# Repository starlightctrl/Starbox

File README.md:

#### WIP Compact Integrated Rectangle Controller

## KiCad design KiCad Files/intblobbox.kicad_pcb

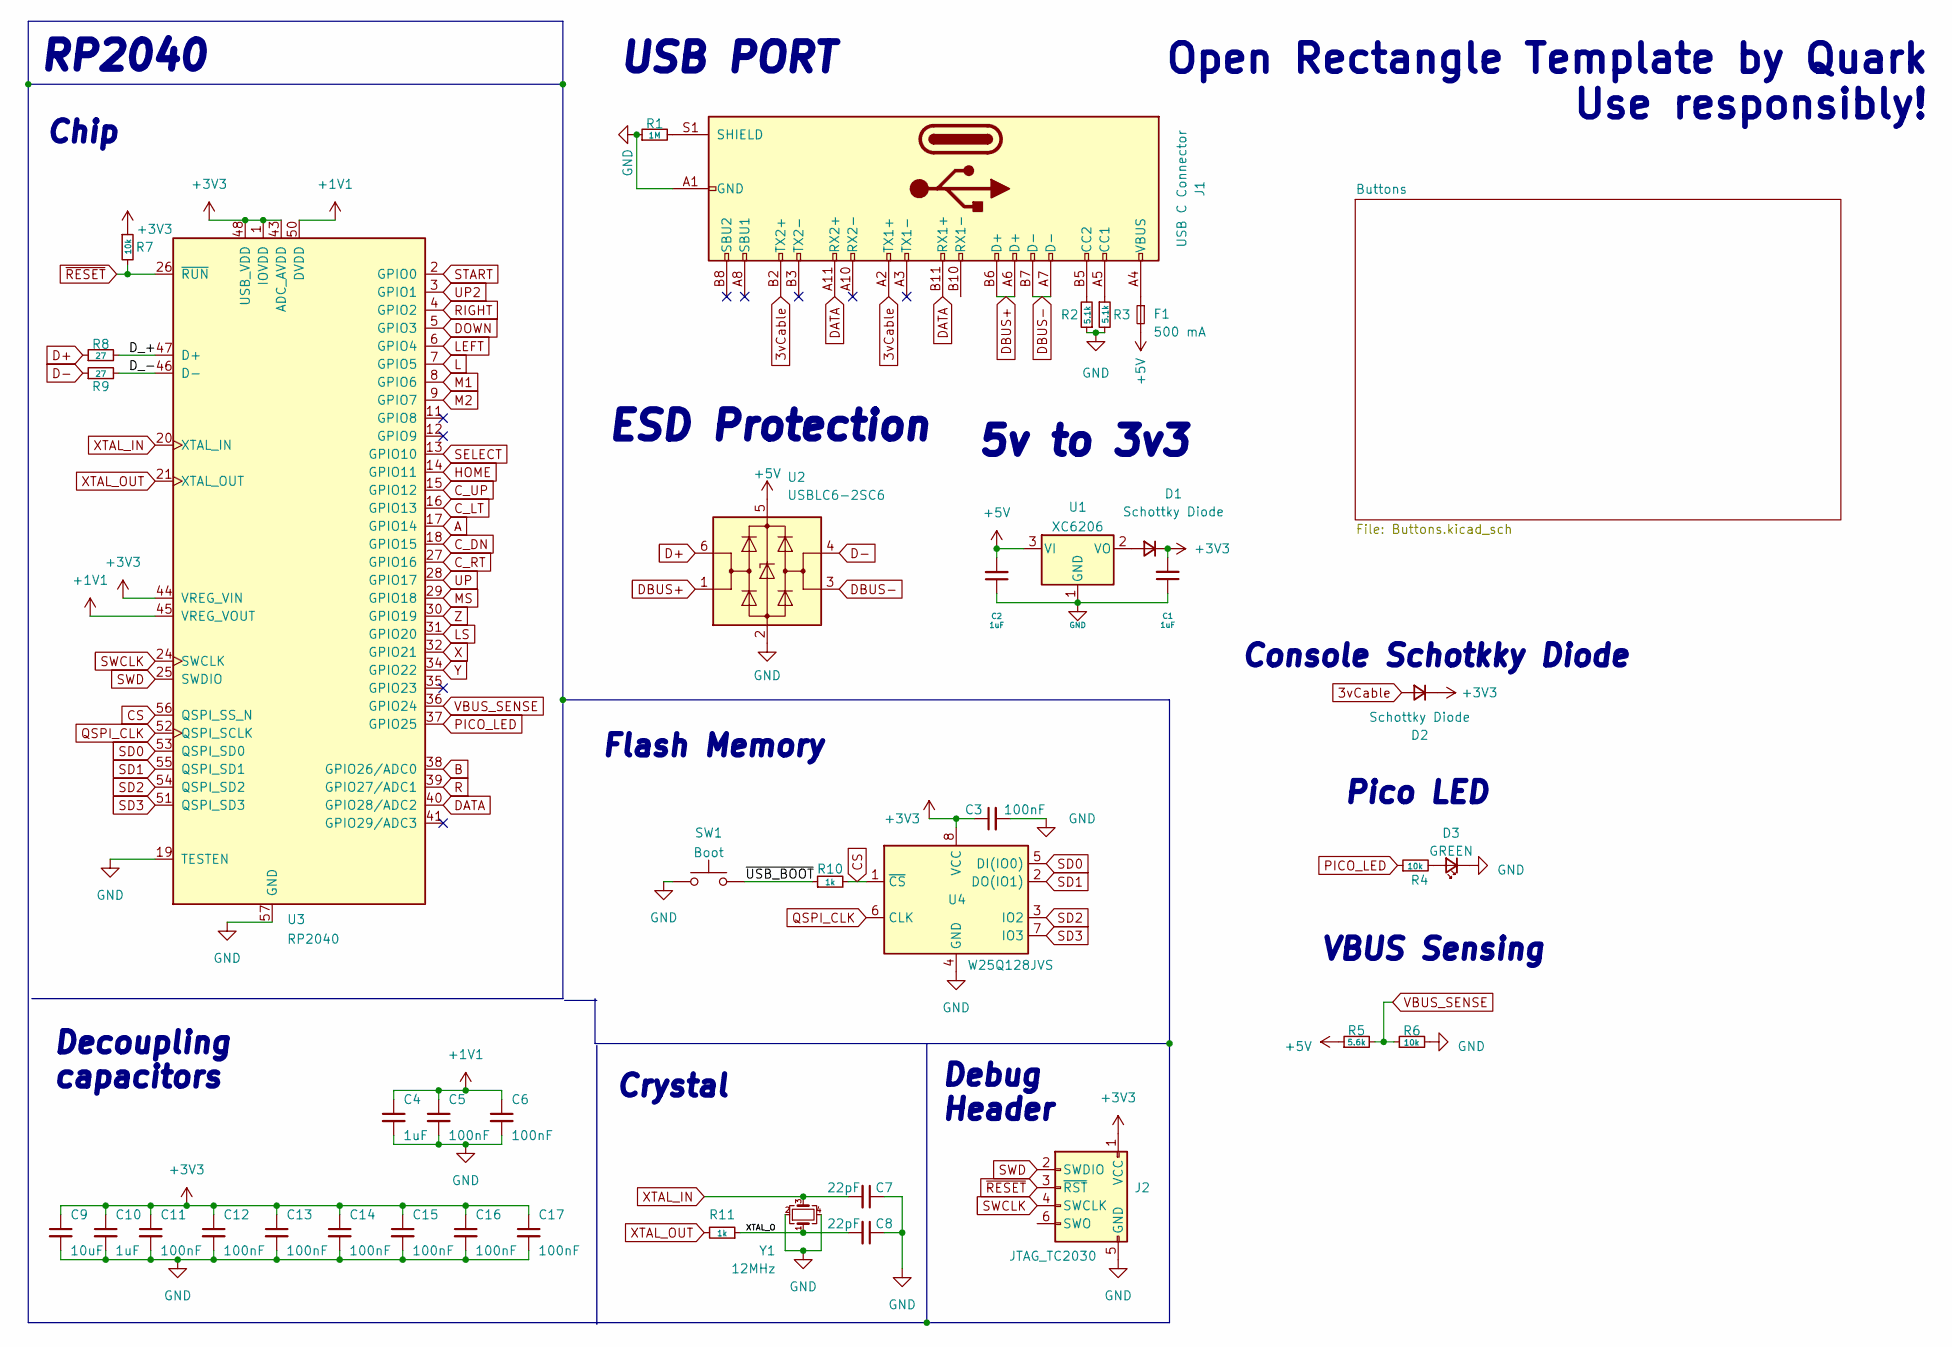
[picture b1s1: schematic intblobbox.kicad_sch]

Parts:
C1, C2, C4, C10: 1uF; C_0402_1005Metric; LCSC C52923
C3, C5, C6, C11, C12, C13, C14, C15, C16, C17: 100nF; C_0402_1005Metric; LCSC C1525
C7, C8: 22pF; C_0402_1005Metric; LCSC C1555
C9: 10uF; C_0402_1005Metric; LCSC C15525
D1, D2: Schottky Diode; D_SOD-123; LCSC C8598
D3: GREEN; LED_0805_2012Metric; LCSC C2297
F1: 500 mA; Fuse_1206_3216Metric; LCSC C70076
J1: USB C Connector; TYPE-C_24P_QCHT; LCSC C456013
J2: JTAG_TC2030; CON_TC2030_outlined
R1: 1M; R_0603_1608Metric; LCSC C22935
R2, R3: 5.1k; R_0402_1005Metric; LCSC C25905
R4, R7: 10k; R_0402_1005Metric; LCSC C25744
R5: 5.6k; R_0603_1608Metric; LCSC C23189
R6: 10k; R_0603_1608Metric; LCSC C25804
R8, R9: 27; R_0603_1608Metric; LCSC C25190
R10, R11: 1k; R_0402_1005Metric; LCSC C11702
SW1: Boot; SW_SPST_SKQG_WithStem; LCSC C318884
U1: XC6206; SOT-23; LCSC C5446
U2: USBLC6-2SC6; SOT-23-6; LCSC C7519
U3: RP2040; RP2040-QFN-56; LCSC C2040
U4: W25Q128JVS; SOIC-8_5.23x5.23mm_P1.27mm; LCSC C97521
Y1: 12MHz; Crystal_SMD_3225-4Pin_3.2x2.5mm; LCSC C9002

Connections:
3vCable: D2.2 (A), J1.A2 (TX1+), J1.B2 (TX2+)
+1V1: C4.1, C5.1, C6.1, U3.23 (DVDD), U3.45 (VREG_VOUT), U3.50 (DVDD)
+3V3: C1.2, C3.1, C9.1, C10.1, C11.1, C12.1, C13.1, C14.1, C15.1, C16.1, C17.1, D1.1 (K), D2.1 (K), J2.1 (VCC), R7.1, U3.1 (IOVDD), U3.10 (IOVDD), U3.22 (IOVDD), U3.33 (IOVDD), U3.42 (IOVDD), U3.43 (ADC_AVDD), U3.44 (VREG_VIN), U3.48 (USB_VDD), U3.49 (IOVDD), U4.8 (VCC)
+5V: C2.2, F1.2, R5.1, U1.3 (VI), U2.5 (VBUS)
/D_+: R8.2, U3.47 (D+)
/D_-: R9.2, U3.46 (D-)
/XTAL_O: C8.2, R11.1, Y1.1
/~USB_BOOT: R10.1, SW1.2
A: U3.17 (GPIO14); also elsewhere on the board
B: U3.38 (GPIO26/ADC0); also elsewhere on the board
CS: R10.2, U3.56 (QSPI_SS_N), U4.1 (~CS)
C_DN: U3.18 (GPIO15); also elsewhere on the board
C_LT: U3.16 (GPIO13); also elsewhere on the board
C_RT: U3.27 (GPIO16); also elsewhere on the board
C_UP: U3.15 (GPIO12); also elsewhere on the board
D+: R8.1, U2.6 (I/O1)
D-: R9.1, U2.4 (I/O2)
DATA: J1.A11 (RX2+), J1.B11 (RX1+), U3.40 (GPIO28/ADC2)
DBUS+: J1.A6 (D+), J1.B6 (D+), U2.1 (I/O1)
DBUS-: J1.A7 (D-), J1.B7 (D-), U2.3 (I/O2)
DOWN: U3.5 (GPIO3); also elsewhere on the board
GND: C1.1, C2.1, C3.2, C4.2, C5.2, C6.2, C7.1, C8.1, C9.2, C10.2, C11.2, C12.2, C13.2, C14.2, C15.2, C16.2, C17.2, D3.1 (K), J1.A1 (GND), J1.A12 (GND), J1.B1 (GND), J1.B12 (GND), J2.5 (GND), R1.1, R2.1, R3.2, R6.2, SW1.1, U1.1 (GND), U2.2 (GND), U3.19 (TESTEN), U3.57 (GND), U4.4 (GND), Y1.2, Y1.4; also elsewhere on the board
HOME: U3.14 (GPIO11); also elsewhere on the board
L: U3.7 (GPIO5); also elsewhere on the board
LEFT: U3.6 (GPIO4); also elsewhere on the board
LS: U3.31 (GPIO20); also elsewhere on the board
M1: U3.8 (GPIO6); also elsewhere on the board
M2: U3.9 (GPIO7); also elsewhere on the board
MS: U3.29 (GPIO18); also elsewhere on the board
unnamed: D1.2 (A), U1.2 (VO)
unnamed: D3.2 (A), R4.2
unnamed: F1.1, J1.A4 (VBUS), J1.A9 (VBUS), J1.B4 (VBUS), J1.B9 (VBUS)
unnamed: J1.A5 (CC1), R3.1
unnamed: J1.B5 (CC2), R2.2
unnamed: J1.S1 (SHIELD), R1.2
PICO_LED: R4.1, U3.37 (GPIO25)
QSPI_CLK: U3.52 (QSPI_SCLK), U4.6 (CLK)
R: U3.39 (GPIO27/ADC1); also elsewhere on the board
RIGHT: U3.4 (GPIO2); also elsewhere on the board
SD0: U3.53 (QSPI_SD0), U4.5 (DI(IO0))
SD1: U3.55 (QSPI_SD1), U4.2 (DO(IO1))
SD2: U3.54 (QSPI_SD2), U4.3 (IO2)
SD3: U3.51 (QSPI_SD3), U4.7 (IO3)
SELECT: U3.13 (GPIO10); also elsewhere on the board
START: U3.2 (GPIO0); also elsewhere on the board
SWCLK: J2.4 (SWCLK), U3.24 (SWCLK)
SWD: J2.2 (SWDIO), U3.25 (SWDIO)
UP: U3.28 (GPIO17); also elsewhere on the board
UP2: U3.3 (GPIO1); also elsewhere on the board
VBUS_SENSE: R5.2, R6.1, U3.36 (GPIO24)
X: U3.32 (GPIO21); also elsewhere on the board
XTAL_IN: C7.2, U3.20 (XTAL_IN), Y1.3
XTAL_OUT: R11.2, U3.21 (XTAL_OUT)
Y: U3.34 (GPIO22); also elsewhere on the board
Z: U3.30 (GPIO19); also elsewhere on the board
~RESET: J2.3 (~RST), R7.2, U3.26 (~RUN)

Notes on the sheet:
Console Schotkky Diode
Crystal
USB PORT
Flash Memory
Pico LED
Open Rectangle Template by Quark Use responsibly!
RP2040
Debug Header
VBUS Sensing
Chip
5v to 3v3
ESD Protection
Decoupling capacitors

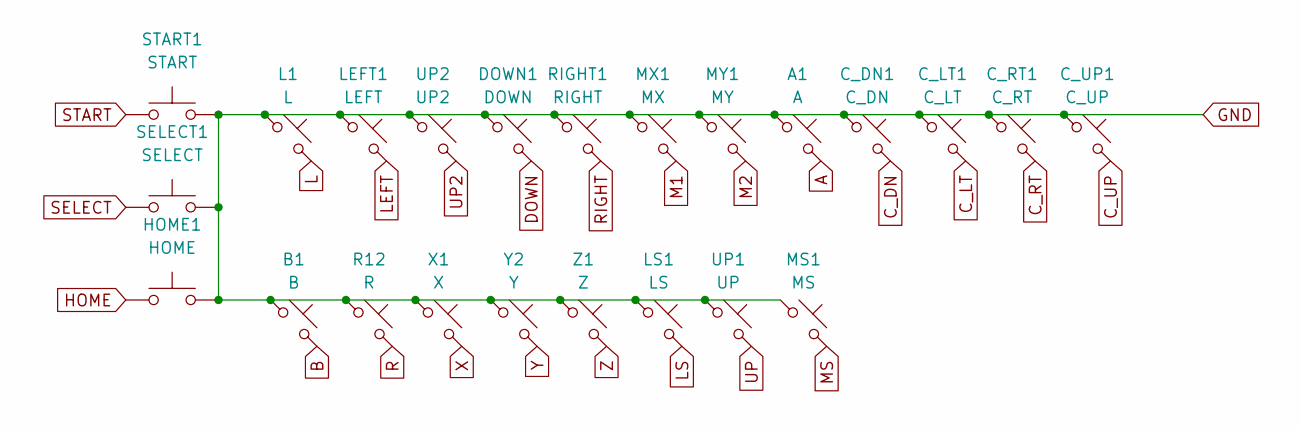
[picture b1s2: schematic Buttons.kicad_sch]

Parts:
A1: A; SW_MX_HS_CPG151101S11_1u
B1: B; SW_MX_HS_CPG151101S11_1u
C_DN1: C_DN; SW_MX_HS_CPG151101S11_1u
C_LT1: C_LT; SW_MX_HS_CPG151101S11_1u
C_RT1: C_RT; SW_MX_HS_CPG151101S11_1u
C_UP1: C_UP; SW_MX_HS_CPG151101S11_1u
DOWN1: DOWN; SW_MX_HS_CPG151101S11_1u
HOME1: HOME; SW_PUSH_6mm_H7.3mm
L1: L; SW_MX_HS_CPG151101S11_1u
LEFT1: LEFT; SW_MX_HS_CPG151101S11_1u
LS1: LS; SW_MX_HS_CPG151101S11_1u
MS1: MS; SW_MX_HS_CPG151101S11_1u
MX1: MX; SW_MX_HS_CPG151101S11_1u
MY1: MY; SW_MX_HS_CPG151101S11_1u
R12: R; SW_MX_HS_CPG151101S11_1u
RIGHT1: RIGHT; SW_MX_HS_CPG151101S11_1u
SELECT1: SELECT; SW_PUSH_6mm_H7.3mm
START1: START; SW_PUSH_6mm_H7.3mm
UP1: UP; SW_MX_HS_CPG151101S11_1u
UP2: UP2; SW_MX_HS_CPG151101S11_1u
X1: X; SW_MX_HS_CPG151101S11_1u
Y2: Y; SW_MX_HS_CPG151101S11_1u
Z1: Z; SW_MX_HS_CPG151101S11_1u

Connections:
A: A1.2; also elsewhere on the board
B: B1.2; also elsewhere on the board
C_DN: C_DN1.2; also elsewhere on the board
C_LT: C_LT1.2; also elsewhere on the board
C_RT: C_RT1.2; also elsewhere on the board
C_UP: C_UP1.2; also elsewhere on the board
DOWN: DOWN1.2; also elsewhere on the board
GND: A1.1, B1.1, C_DN1.1, C_LT1.1, C_RT1.1, C_UP1.1, DOWN1.1, HOME1.2, L1.1, LEFT1.1, LS1.1, MS1.1, MX1.1, MY1.1, R12.1, RIGHT1.1, SELECT1.2, START1.2, UP1.1, UP2.1, X1.1, Y2.1, Z1.1; also elsewhere on the board
HOME: HOME1.1; also elsewhere on the board
L: L1.2; also elsewhere on the board
LEFT: LEFT1.2; also elsewhere on the board
LS: LS1.2; also elsewhere on the board
M1: MX1.2; also elsewhere on the board
M2: MY1.2; also elsewhere on the board
MS: MS1.2; also elsewhere on the board
R: R12.2; also elsewhere on the board
RIGHT: RIGHT1.2; also elsewhere on the board
SELECT: SELECT1.1; also elsewhere on the board
START: START1.1; also elsewhere on the board
UP: UP1.2; also elsewhere on the board
UP2: UP2.2; also elsewhere on the board
X: X1.2; also elsewhere on the board
Y: Y2.2; also elsewhere on the board
Z: Z1.2; also elsewhere on the board

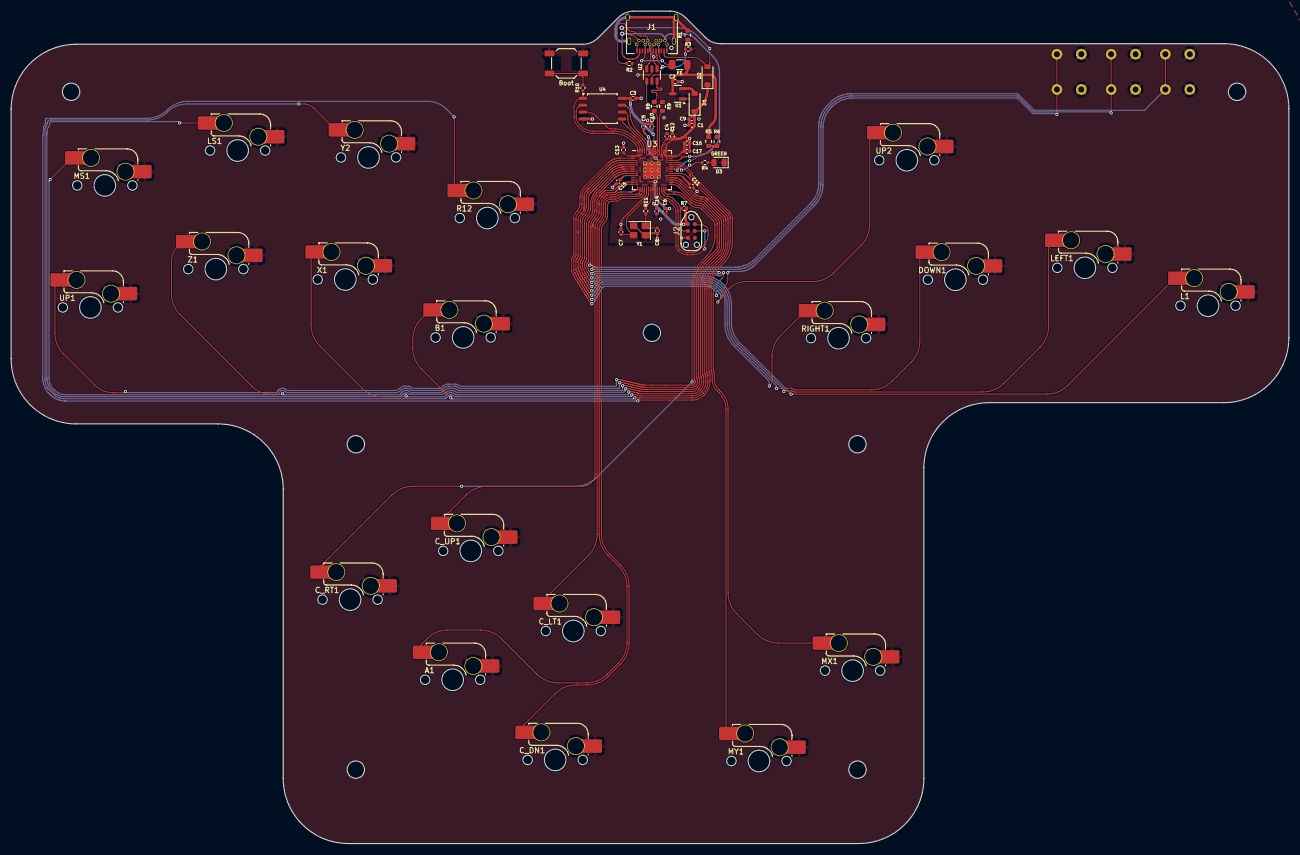
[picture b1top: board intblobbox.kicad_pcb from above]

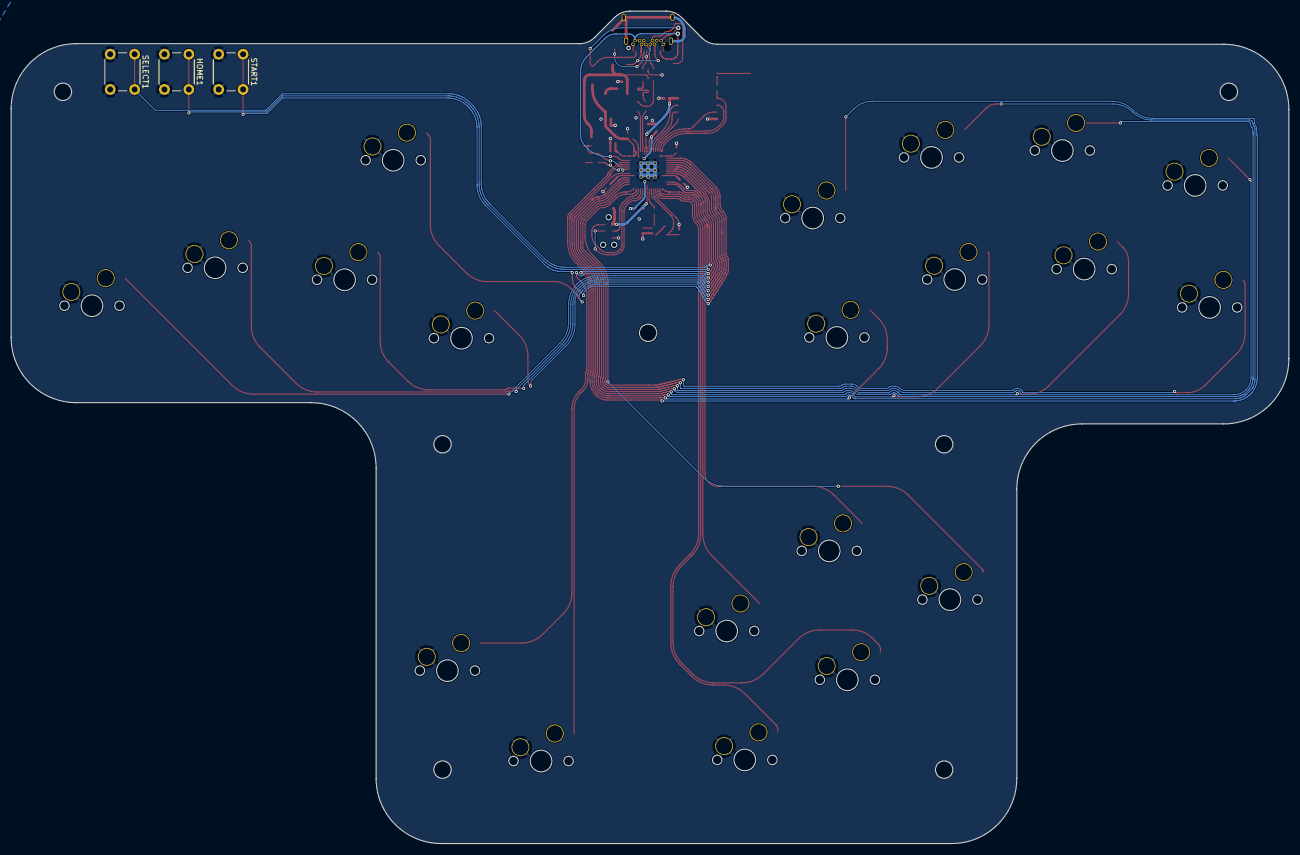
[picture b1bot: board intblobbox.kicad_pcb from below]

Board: 2 copper layers, 235.6 x 153.5 mm, 63 parts (3 on the bottom side), 56 nets.

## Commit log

2024-08-07 Initial commit. README.md plus a KiCad PCB files added.
